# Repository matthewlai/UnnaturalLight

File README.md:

# UnnaturalLight

Lamp with colour temperature setting.

[Introduction](https://dubiouscreations.com/2017/12/02/unnaturallight-part-1-mechanical-optical-design/)

[Mechanical / Optical Design](https://dubiouscreations.com/2017/12/02/unnaturallight-part-1-mechanical-optical-design/)

[Electronics / Firmware Design](https://dubiouscreations.com/2018/01/06/unnaturallight-part-2-electrical-design/)

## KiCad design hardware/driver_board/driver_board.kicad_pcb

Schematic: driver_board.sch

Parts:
C1: 0.1uF; C_0805
C2: 1uF; C_0805
C3: 220uF; CP_Radial_D8.0mm_P3.80mm
F1: Fuse; Fuse_SMD1206_HandSoldering
J1: BARREL_JACK; Kobiconn_163-179PH-EX
J2: CONN_01X03; Pin_Header_Straight_1x03_Pitch2.54mm
J3: CONN_01X06; Molex_53047_0610
P1: Power; Socket_Strip_Arduino_1x08
P2: Analog; Socket_Strip_Arduino_1x06
P3: Digital; Socket_Strip_Arduino_1x10
P4: Digital; Socket_Strip_Arduino_1x08
P5, P6, P7, P8: CONN_01X01; Arduino_1pin
Q1, Q2: Q_NMOS_GDS; TO-263-3_TabPin2
R1, R2: 10KR; R_0805
U1: MIC4124; SOIC-8-N

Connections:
+3V3: P1.4
+5V: J3.6, P1.5
/0(Rx): P4.8
/1(Tx): P4.7
/2: P4.6
/3(**): P4.5
/4: P4.4
/5(**): P4.3
/6(**): P4.2
/7: P4.1
/8: P3.10
/9(**): P3.9, R1.1, U1.2
/10(**/SS): P3.8, R2.1, U1.4
/11(**/MOSI): P3.7
/12(MISO): P3.6
/13(SCK): P3.5
/A0: J3.5, P2.1
/A1: J3.4, P2.2
/A2: J3.3, P2.3
/A3: J3.2, P2.4
/A4(SDA): P2.5
/A4(SDA)_2: P3.2
/A5(SCL): P2.6
/A5(SCL)_2: P3.1
/AREF: P3.3
/C_LED: J2.3, Q1.2
/IOREF: P1.2
/Reset: P1.3
/W_LED: J2.2, Q2.2
GND: C1.2, C2.2, C3.2, J1.2, J1.3, J3.1, P1.6, P1.7, P3.4, Q1.3, Q2.3, R1.2, R2.2, U1.3
unnamed: F1.2, J1.1
unnamed: Q1.1, U1.7
unnamed: Q2.1, U1.5
VCC: C1.1, C2.1, C3.1, F1.1, J2.1, P1.8, U1.6

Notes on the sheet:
Holes
Shield for Arduino that uses the same pin disposition like "Uno" board Rev 3.
IPB22N03

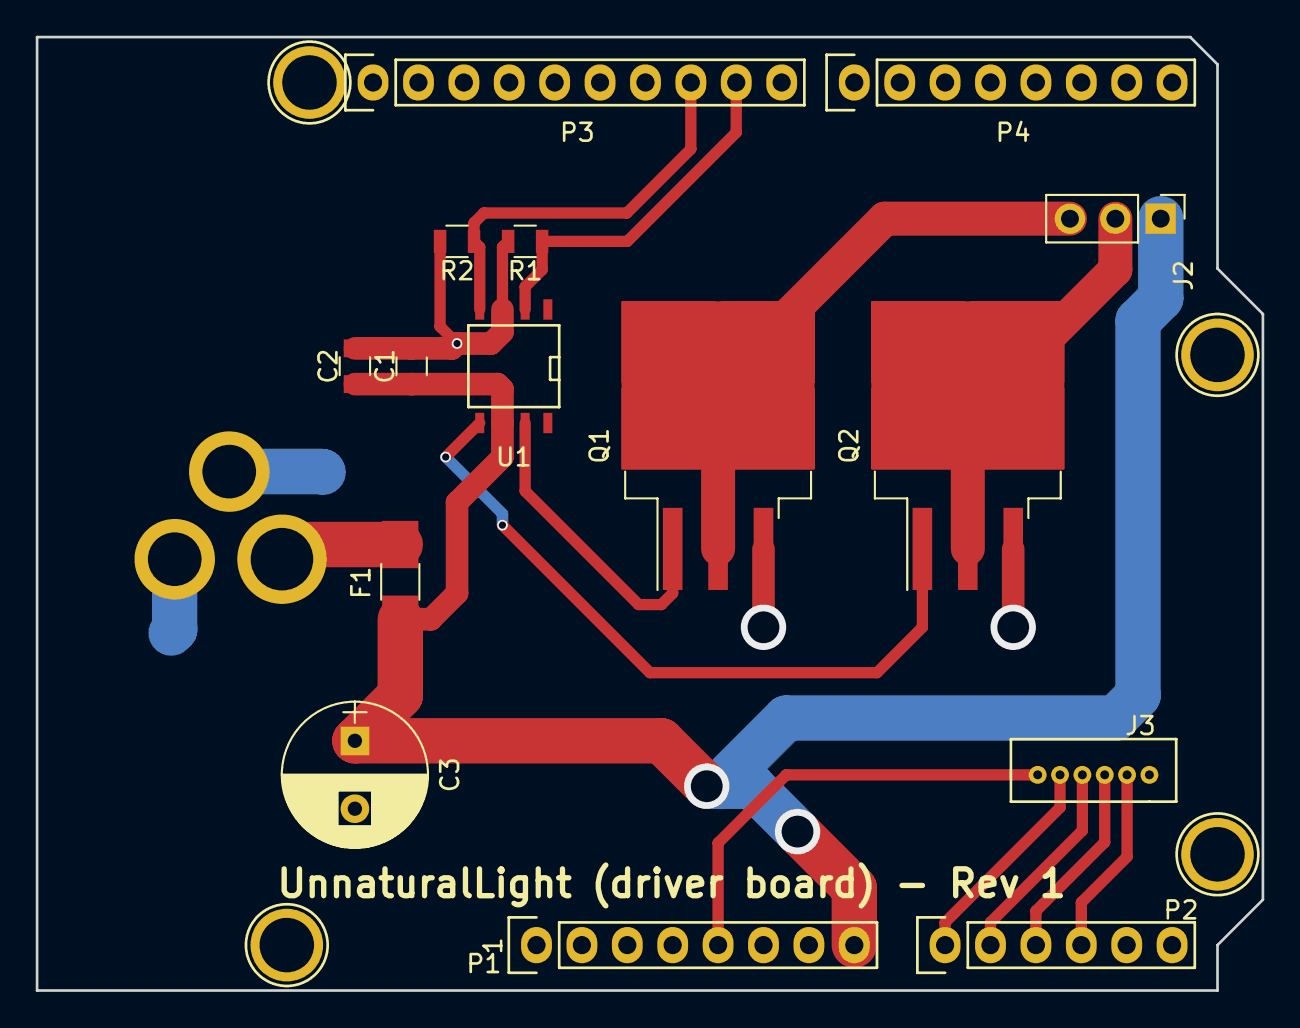
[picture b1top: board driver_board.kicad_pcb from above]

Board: 2 copper layers, 68.6 x 53.3 mm, 20 parts (1 on the bottom side), 14 nets.

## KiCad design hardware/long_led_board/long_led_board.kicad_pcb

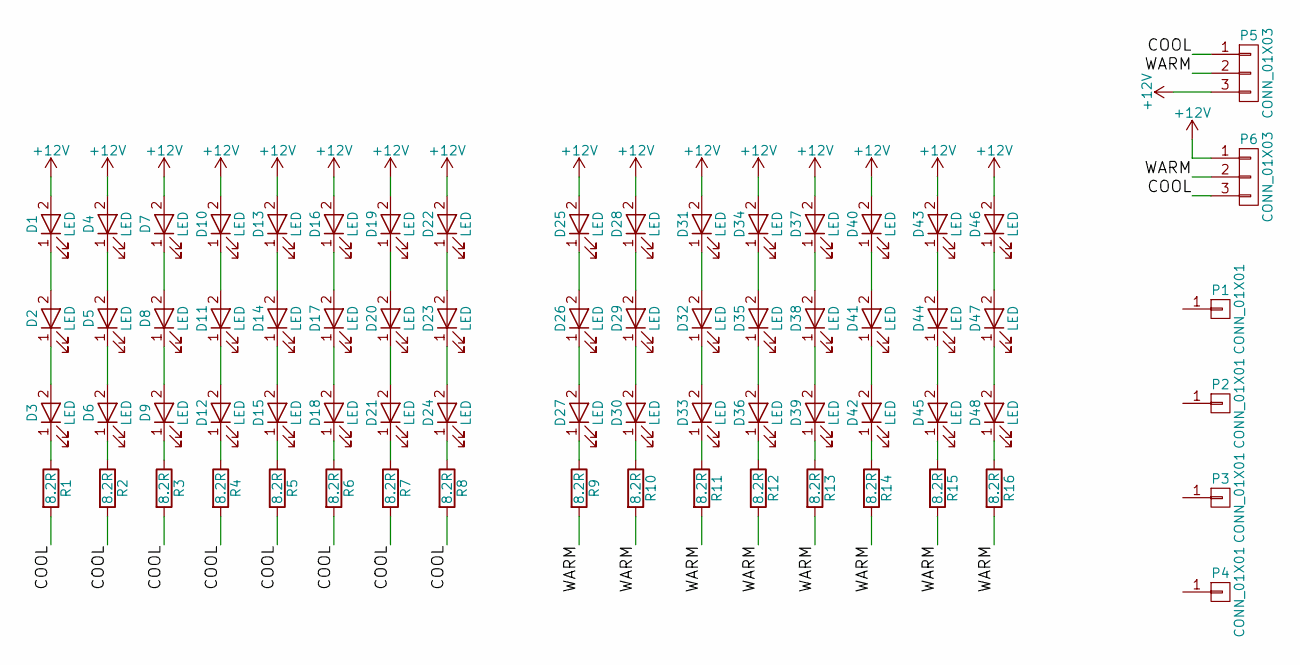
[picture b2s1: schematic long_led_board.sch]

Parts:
D1, D2, D3, D4, D5, D6, D7, D8, D9, D10, D11, D12, D13, D14, D15, D16, D17, D18, D19, D20, D21, D22, D23, D24, D25, D26, D27, D28, D29, D30, D31, D32, D33, D34, D35, D36, D37, D38, D39, D40, D41, D42, D43, D44, D45, D46, D47, D48: LED; LED3030
P1, P2, P3, P4: CONN_01X01; M3
P5, P6: CONN_01X03; AMPMODU_MOD_II_3PIN
R1, R2, R3, R4, R5, R6, R7, R8, R9, R10, R11, R12, R13, R14, R15, R16: 8.2R; R_2512

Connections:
+12V: D1.2 (A), D4.2 (A), D7.2 (A), D10.2 (A), D13.2 (A), D16.2 (A), D19.2 (A), D22.2 (A), D25.2 (A), D28.2 (A), D31.2 (A), D34.2 (A), D37.2 (A), D40.2 (A), D43.2 (A), D46.2 (A), P5.3, P6.1
/COOL: P5.1, P6.3, R1.2, R2.2, R3.2, R4.2, R5.2, R6.2, R7.2, R8.2
/WARM: P5.2, P6.2, R9.2, R10.2, R11.2, R12.2, R13.2, R14.2, R15.2, R16.2
unnamed: D1.1 (K), D2.2 (A)
unnamed: D2.1 (K), D3.2 (A)
unnamed: D3.1 (K), R1.1
unnamed: D4.1 (K), D5.2 (A)
unnamed: D5.1 (K), D6.2 (A)
unnamed: D6.1 (K), R2.1
unnamed: D7.1 (K), D8.2 (A)
unnamed: D8.1 (K), D9.2 (A)
unnamed: D9.1 (K), R3.1
unnamed: D10.1 (K), D11.2 (A)
unnamed: D11.1 (K), D12.2 (A)
unnamed: D12.1 (K), R4.1
unnamed: D13.1 (K), D14.2 (A)
unnamed: D14.1 (K), D15.2 (A)
unnamed: D15.1 (K), R5.1
unnamed: D16.1 (K), D17.2 (A)
unnamed: D17.1 (K), D18.2 (A)
unnamed: D18.1 (K), R6.1
unnamed: D19.1 (K), D20.2 (A)
unnamed: D20.1 (K), D21.2 (A)
unnamed: D21.1 (K), R7.1
unnamed: D22.1 (K), D23.2 (A)
unnamed: D23.1 (K), D24.2 (A)
unnamed: D24.1 (K), R8.1
unnamed: D25.1 (K), D26.2 (A)
unnamed: D26.1 (K), D27.2 (A)
unnamed: D27.1 (K), R9.1
unnamed: D28.1 (K), D29.2 (A)
unnamed: D29.1 (K), D30.2 (A)
unnamed: D30.1 (K), R10.1
unnamed: D31.1 (K), D32.2 (A)
unnamed: D32.1 (K), D33.2 (A)
unnamed: D33.1 (K), R11.1
unnamed: D34.1 (K), D35.2 (A)
unnamed: D35.1 (K), D36.2 (A)
unnamed: D36.1 (K), R12.1
unnamed: D37.1 (K), D38.2 (A)
unnamed: D38.1 (K), D39.2 (A)
unnamed: D39.1 (K), R13.1
unnamed: D40.1 (K), D41.2 (A)
unnamed: D41.1 (K), D42.2 (A)
unnamed: D42.1 (K), R14.1
unnamed: D43.1 (K), D44.2 (A)
unnamed: D44.1 (K), D45.2 (A)
unnamed: D45.1 (K), R15.1
unnamed: D46.1 (K), D47.2 (A)
unnamed: D47.1 (K), D48.2 (A)
unnamed: D48.1 (K), R16.1

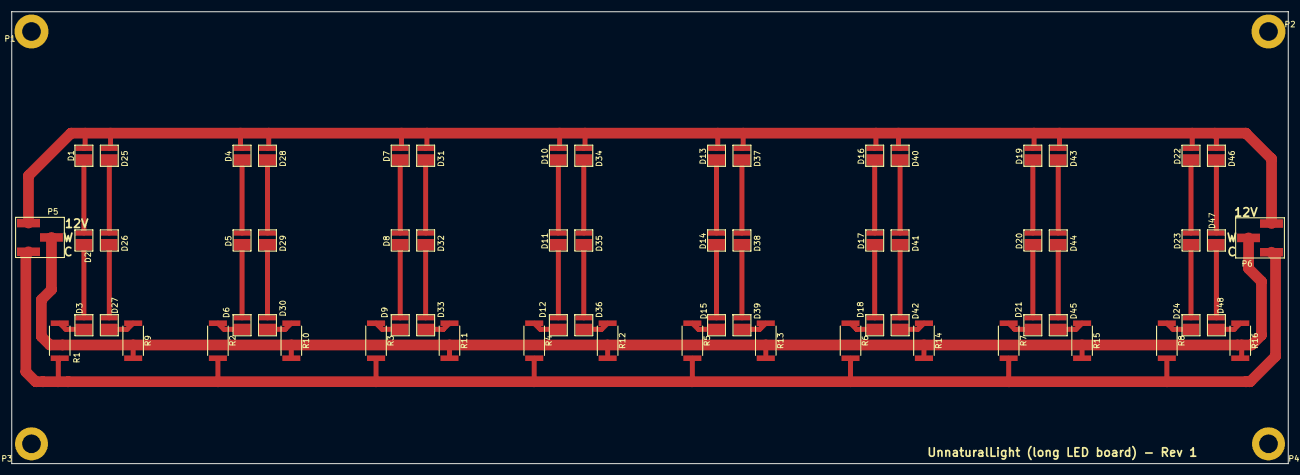
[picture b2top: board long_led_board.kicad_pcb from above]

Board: 2 copper layers, 226.0 x 80.0 mm, 70 parts (0 on the bottom side), 51 nets.

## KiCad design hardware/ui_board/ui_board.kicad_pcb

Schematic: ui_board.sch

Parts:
J1: CONN_01X06; Molex_53047_0610
R1: 10KR; R_0805_HandSoldering
RV1, RV2: POT; M_POT
SW1: SW_SPST; CWSA11AAN1S

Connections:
/POT1: J1.4, RV1.2
/POT2: J1.3, RV2.2
/SW: J1.2, R1.1, SW1.1
GND: J1.6, RV1.3, RV2.3, SW1.2
VCC: J1.1, R1.2, RV1.1, RV2.1

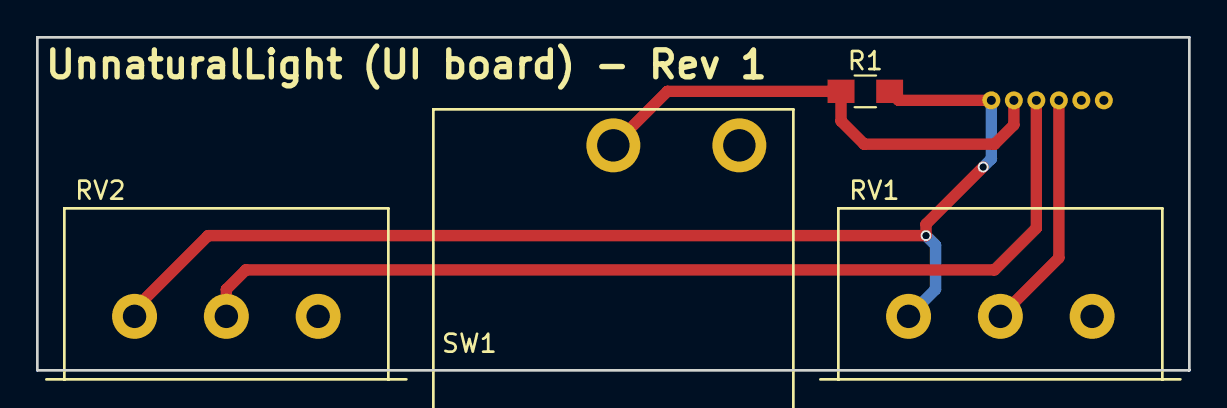
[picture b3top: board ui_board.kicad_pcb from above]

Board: 2 copper layers, 64.0 x 18.5 mm, 5 parts (1 on the bottom side), 5 nets.

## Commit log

2015-05-09 Changed C standard to c11
2015-05-09 Renamed WifiLED.c to WifiLED.cpp
2015-05-09 Added CDCADM support
2015-05-09 Added ignore file
2016-12-19 Added hardware
2017-02-04 Improved flashing script to tell the bootloader we have 3.3V supply (and flash faster)
2017-02-04 Added more files to remove for "make clean"
2017-02-04 Improved cdcacm and added other support files
2017-02-04 Added testing code to WifiLED.cpp (moving computer).
2017-02-04 Added hardware design for WifiLED
2017-02-04 Merge
2017-02-04 Trying to clean up a merge conflict mess
2017-10-11 Removed libopencm3 and software
2017-10-11 Cleaned up for git import
2017-10-11 Cleaned up after import from Hg
2017-10-11 Created README
2017-10-11 Initial commit of driver and UI boards
2017-10-15 Finished rev1 PCBs
2017-10-15 Updated README with new name
2017-10-29 Added fab files
2017-11-05 Changed LED board connectors to SMD
2017-11-10 Added long LED board design
2017-11-23 Added paste dxfs
2018-03-04 Added arduino firmware
